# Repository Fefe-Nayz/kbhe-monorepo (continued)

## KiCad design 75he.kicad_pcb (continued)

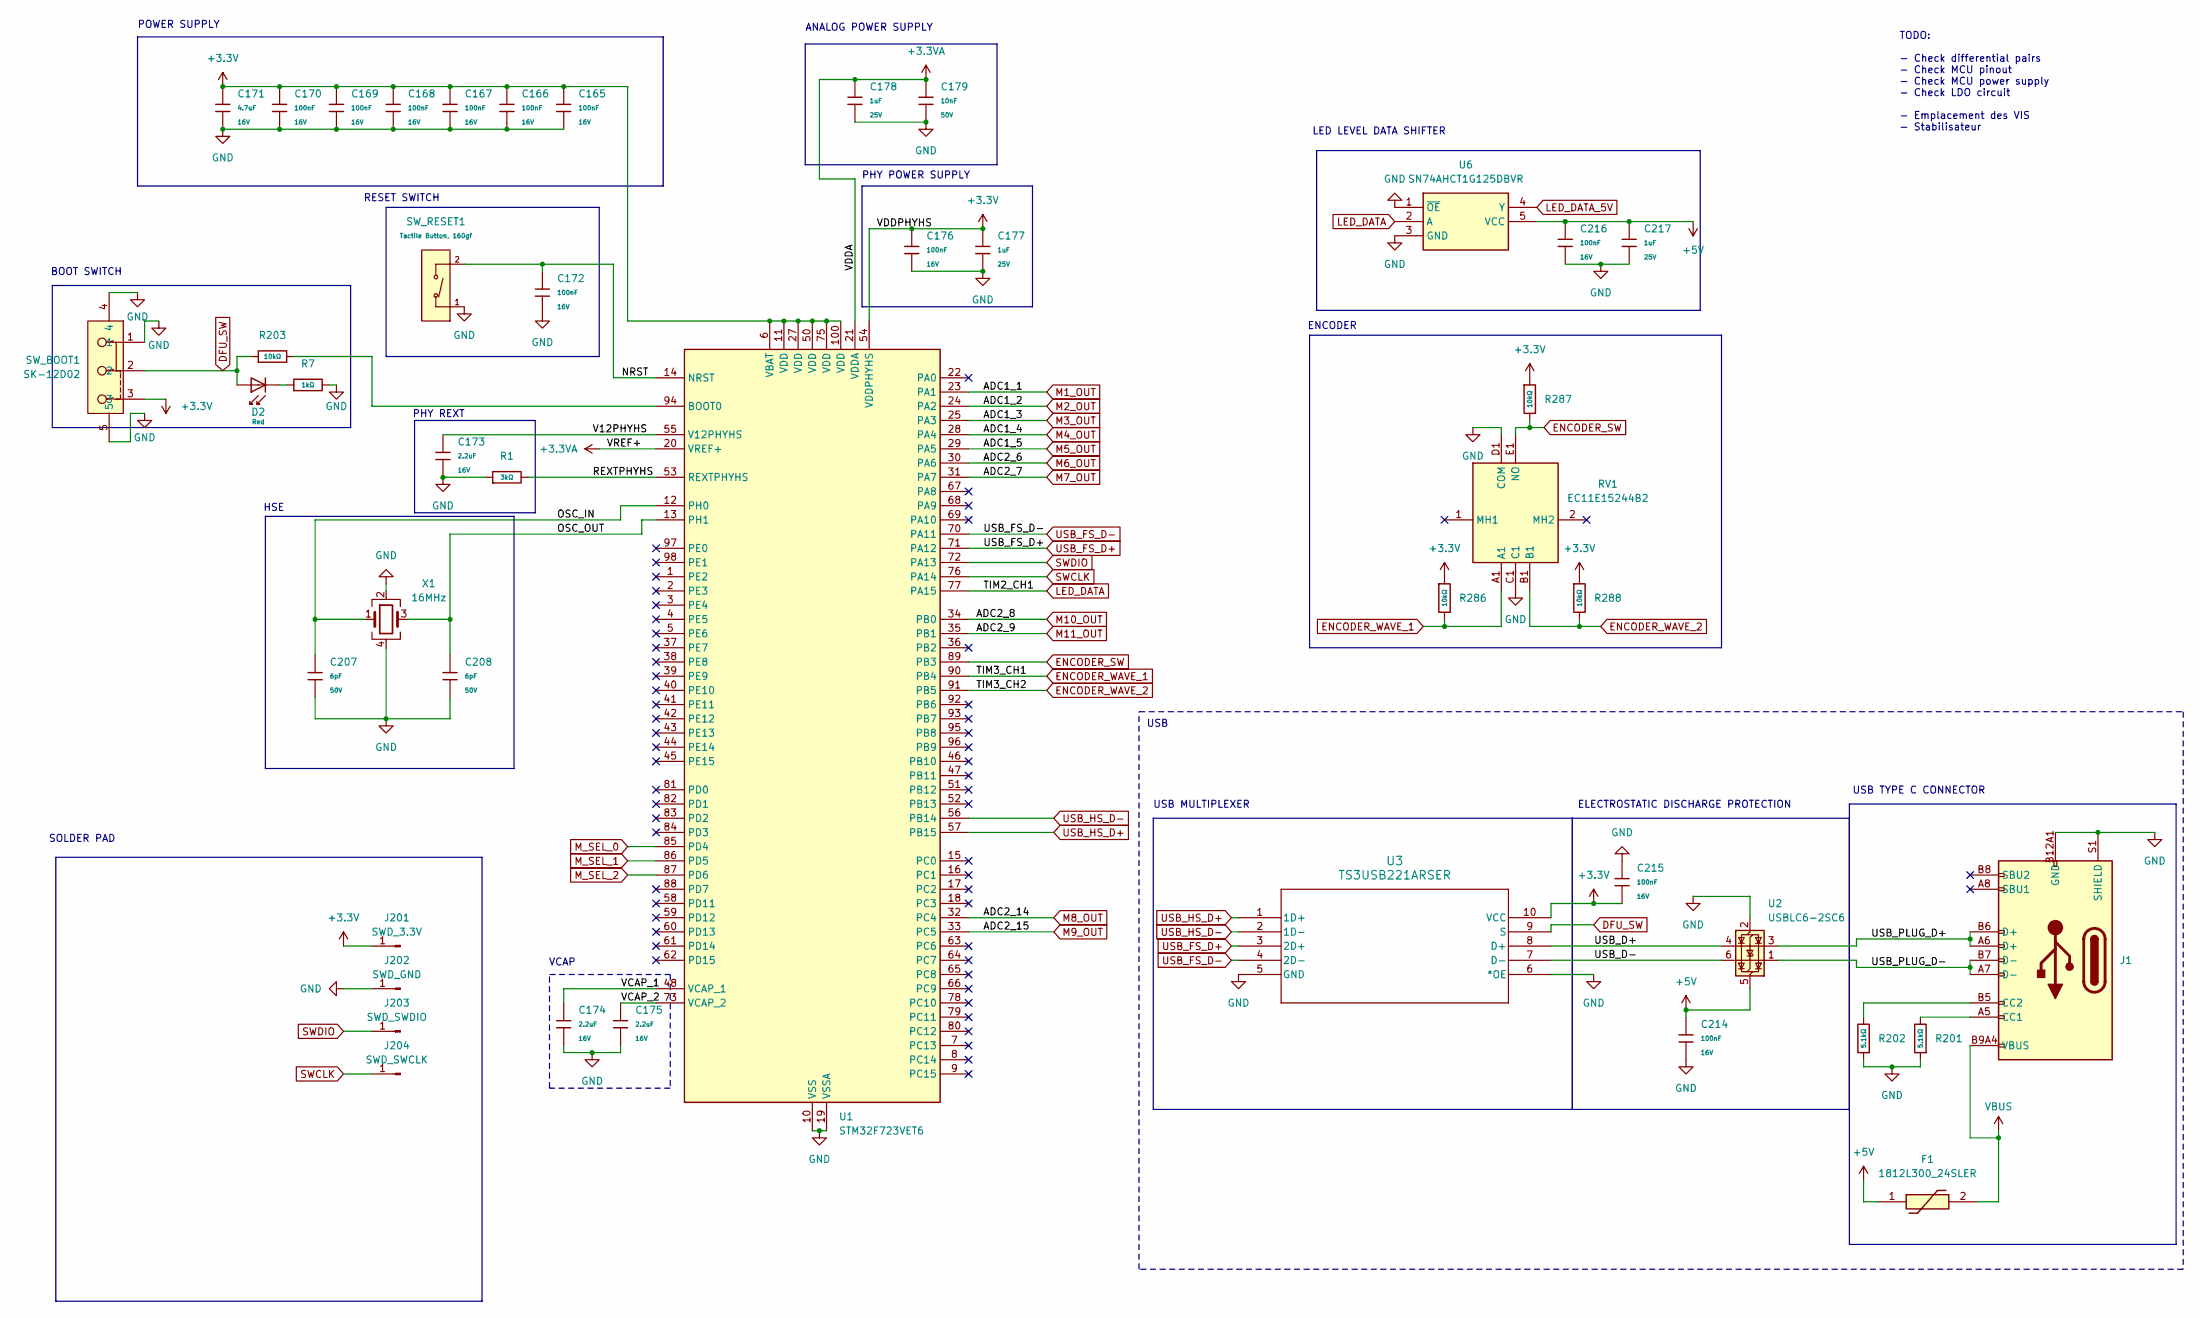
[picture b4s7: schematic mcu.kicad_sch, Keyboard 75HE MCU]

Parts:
C165, C166, C167, C168, C169, C170, C172, C176, C214, C215, C216: 100nF; C_0402; Voltage Rated 16V; Tolerance ±10%; Part CL05B104KO5NNNC; LCSC C1525
C171: 4.7uF; C_0603; Voltage Rated 16V; Tolerance ±10%; Part CL10A475KO8NNNC; LCSC C19666
C173, C174, C175: 2.2uF; C_0603; Voltage Rated 16V; Tolerance ±10%; Part CL10A225KO8NNNC; LCSC C23630
C177, C178, C217: 1uF; C_0402; Voltage Rated 25V; Tolerance ±10%; Part CL05A105KA5NQNC; LCSC C52923
C179: 10nF; C_0402; Voltage Rated 50V; Tolerance ±10%; Part CL05B103KB5NNNC; LCSC C15195
C207, C208: 6pF; C_0603; Voltage Rated 50V; Part 0603CG6R0C500NT; LCSC C37474
D2: Red; D_0603; Part KT-0603R; LCSC C2286
F1: 1812L300_24SLER; 1812L190SLPR; Mouser Part Number 576-1812L300/24SLER
J1: Connector, USB-TYPE-C-16P; TYPE-C-SMD_HX-TYPE-C-16PIN; LCSC C2927039
J201: SWD_3.3V; SolderWirePad_1x01_SMD_2x4mm
J202: SWD_GND; SolderWirePad_1x01_SMD_2x4mm
J203: SWD_SWDIO; SolderWirePad_1x01_SMD_2x4mm
J204: SWD_SWCLK; SolderWirePad_1x01_SMD_2x4mm
R1: 3kΩ; R_0603; Overload Voltage (Max) 75V; Tolerance ±1%; Part 0603WAF3001T5E; LCSC C4211
R7: 1kΩ; R_0402; Overload Voltage (Max) 50V; Tolerance ±1%; Part 0402WGF1001TCE; LCSC C11702
R201, R202: 5.1kΩ; R_0402; Overload Voltage (Max) 50V; Tolerance ±1%; Part 0402WGF5101TCE; LCSC C25905
R203, R286, R287, R288: 10kΩ; R_0402; Overload Voltage (Max) 50V; Tolerance ±1%; Part 0402WGF1002TCE; LCSC C25744
RV1: EC11E15244B2; Mouser Part Number 688-EC11E15244B2
SW_BOOT1: SK-12D02; SW-TH_SK-12D02VG3; LCSC Part C131374
SW_RESET1: Tactile Button, 160gf; SW_TS-1088-AR02016; Voltage Rating (Dc) 12V; Part TS-1088-AR02016; LCSC C720477
U1: STM32F723VET6; LQFP-100_14x14mm_P0.5mm
U2: USBLC6-2SC6; SOT-23-6
U3: TS3USB221ARSER; RSE10
U6: SN74AHCT1G125DBVR; SOT95P280X145-5N; Manufacturer_Part_Number SN74AHCT1G125DBVR; Mouser Part Number 595-SNAHCT1G125DBVR
X1: 16MHz; Crystal_SMD_2520-4Pin_2.5x2.0mm; LCSC C280836

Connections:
+3.3V: C165.1, C166.1, C167.1, C168.1, C169.1, C170.1, C171.1, C176.1, C177.1, C215.2, J201.1, R286.1, R287.1, R288.1, SW_BOOT1.3, U1.6 (VBAT), U1.11 (VDD), U1.27 (VDD), U1.50 (VDD), U1.54 (VDDPHYHS), U1.75 (VDD), U1.100 (VDD), U3.10 (VCC); also elsewhere on the board
+3.3VA: C178.1, C179.1, U1.20 (VREF+), U1.21 (VDDA); also elsewhere on the board
+5V: C214.1, C216.1, C217.1, F1.1, U2.5 (VBUS); also elsewhere on the board
/MCU/NRST: C172.1, SW_RESET1.2 (B), U1.14 (NRST)
/MCU/OSC_IN: C207.1, U1.12 (PH0), X1.1
/MCU/OSC_OUT: C208.1, U1.13 (PH1), X1.3
/MCU/REXTPHYHS: R1.2, U1.53 (REXTPHYHS)
/MCU/USB_D+: U2.4 (I/O2), U3.8 (D+)
/MCU/USB_D-: U2.6 (I/O1), U3.7 (D-)
/MCU/USB_PLUG_D+: J1.A6 (D+), J1.B6 (D+), U2.3 (I/O2)
/MCU/USB_PLUG_D-: J1.A7 (D-), J1.B7 (D-), U2.1 (I/O1)
/MCU/V12PHYHS: C173.1, U1.55 (V12PHYHS)
/MCU/VCAP_1: C174.1, U1.48 (VCAP_1)
/MCU/VCAP_2: C175.1, U1.73 (VCAP_2)
DFU_SW: D2.2, R203.1, SW_BOOT1.2, U3.9 (S)
ENCODER_SW: R287.2, RV1.E1 (NO), U1.89 (PB3)
ENCODER_WAVE_1: R286.2, RV1.A1, U1.90 (PB4)
ENCODER_WAVE_2: R288.2, RV1.B1, U1.91 (PB5)
GND: C165.2, C166.2, C167.2, C168.2, C169.2, C170.2, C171.2, C172.2, C173.2, C174.2, C175.2, C176.2, C177.2, C178.2, C179.2, C207.2, C208.2, C214.2, C215.1, C216.2, C217.2, J1.A12B1 (GND), J1.B12A1 (GND), J1.S1 (SHIELD), J202.1, R1.1, R7.2, R201.1, R202.1, RV1.C1, RV1.D1 (COM), SW_BOOT1.1, SW_BOOT1.4, SW_BOOT1.5, SW_RESET1.1 (A), U1.10 (VSS), U1.19 (VSSA), U1.26 (VSS), U1.49 (VSS), U1.74 (VSS), U1.99 (VSS), U2.2 (GND), U3.5 (GND), U3.6 (*OE), X1.2, X1.4; also elsewhere on the board
LED_DATA: U1.77 (PA15), U6.2 (A)
M1_OUT: U1.23 (PA1); also elsewhere on the board
M2_OUT: U1.24 (PA2); also elsewhere on the board
M3_OUT: U1.25 (PA3); also elsewhere on the board
M4_OUT: U1.28 (PA4); also elsewhere on the board
M5_OUT: U1.29 (PA5); also elsewhere on the board
M6_OUT: U1.30 (PA6); also elsewhere on the board
M7_OUT: U1.31 (PA7); also elsewhere on the board
M8_OUT: U1.32 (PC4); also elsewhere on the board
M9_OUT: U1.33 (PC5); also elsewhere on the board
M10_OUT: U1.34 (PB0); also elsewhere on the board
M11_OUT: U1.35 (PB1); also elsewhere on the board
M_SEL_0: U1.85 (PD4); also elsewhere on the board
M_SEL_1: U1.86 (PD5); also elsewhere on the board
M_SEL_2: U1.87 (PD6); also elsewhere on the board
unnamed: D2.1, R7.1
unnamed: J1.A5 (CC1), R201.2
unnamed: J1.B5 (CC2), R202.2
unnamed: R203.2, U1.94 (BOOT0)
SWCLK: J204.1, U1.76 (PA14)
SWDIO: J203.1, U1.72 (PA13)
USB_FS_D+: U1.71 (PA12), U3.3 (2D+)
USB_FS_D-: U1.70 (PA11), U3.4 (2D-)
USB_HS_D+: U1.57 (PB15), U3.1 (1D+)
USB_HS_D-: U1.56 (PB14), U3.2 (1D-)
VBUS: F1.2, J1.A9B4 (VBUS), J1.B9A4 (VBUS)

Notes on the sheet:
HSE
ANALOG POWER SUPPLY
PHY POWER SUPPLY
TODO: - Check differential pairs - Check MCU pinout - Check MCU power supply - Check LDO circuit - Emplacement des VIS - Stabilisateur
USB TYPE C CONNECTOR
ELECTROSTATIC DISCHARGE PROTECTION
SOLDER PAD
LED LEVEL DATA SHIFTER
VCAP
BOOT SWITCH
ENCODER
RESET SWITCH
USB MULTIPLEXER
USB
POWER SUPPLY
PHY REXT

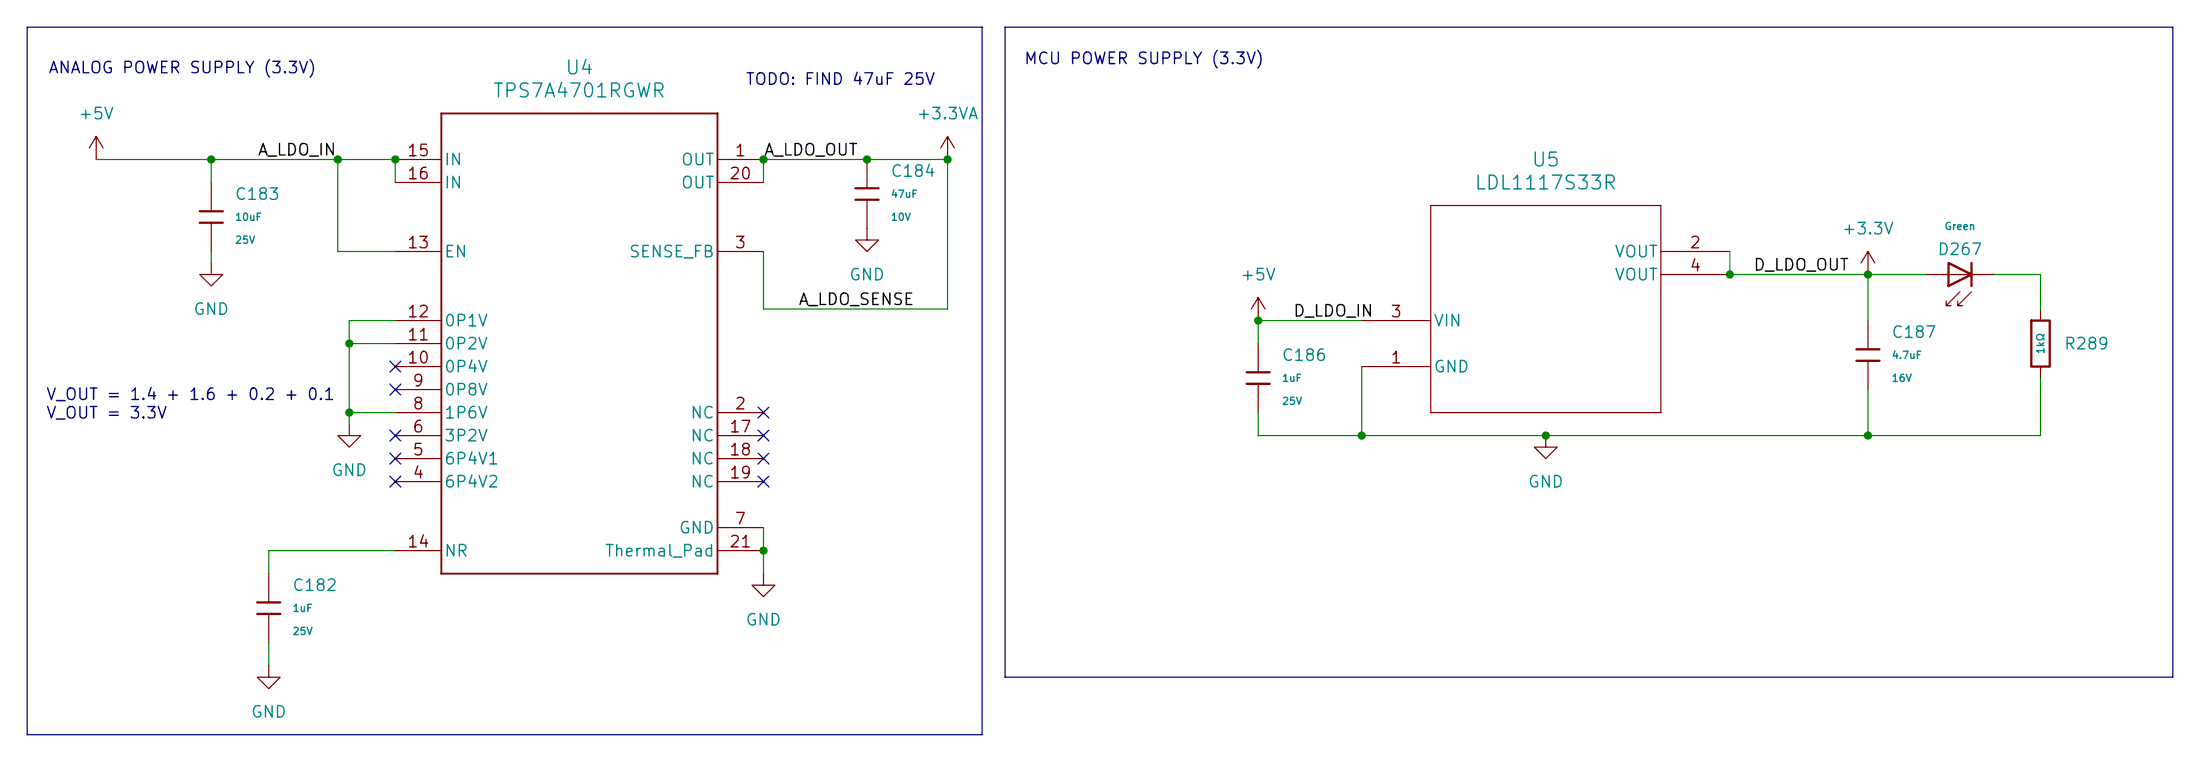
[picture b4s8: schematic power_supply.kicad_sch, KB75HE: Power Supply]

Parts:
C182, C186: 1uF; C_0402; Voltage Rated 25V; Tolerance ±10%; Part CL05A105KA5NQNC; LCSC C52923
C183: 10uF; C_0805; Voltage Rated 25V; Tolerance ±10%; Part CL21A106KAYNNNE; LCSC C15850
C184: 47uF; C_1206; Voltage Rated 10V; Tolerance ±20%; Part CL31A476MPHNNNE; LCSC C96123
C187: 4.7uF; C_0603; Voltage Rated 16V; Tolerance ±10%; Part CL10A475KO8NNNC; LCSC C19666
D267: Green; D_0805; Part KT-0805G; LCSC C2297
R289: 1kΩ; R_0402; Overload Voltage (Max) 50V; Tolerance ±1%; Part 0402WGF1001TCE; LCSC C11702
U4: TPS7A4701RGWR; RGW0020A-IPC_A; LCSC C90084
U5: LDL1117S33R; SOT223_STM

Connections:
+3.3V: C187.1, D267.2, U5.2 (VOUT), U5.4 (VOUT); also elsewhere on the board
+3.3VA: C184.1, U4.1 (OUT), U4.3 (SENSE_FB), U4.20 (OUT); also elsewhere on the board
+5V: C183.1, C186.1, U4.13 (EN), U4.15 (IN), U4.16 (IN), U5.3 (VIN); also elsewhere on the board
GND: C182.2, C183.2, C184.2, C186.2, C187.2, R289.2, U4.7 (GND), U4.8 (1P6V), U4.11 (0P2V), U4.12 (0P1V), U4.21 (Thermal_Pad), U5.1 (GND); also elsewhere on the board
unnamed: D267.1, R289.1
unnamed: C182.1, U4.14 (NR)

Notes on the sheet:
TODO: FIND 47uF 25V
ANALOG POWER SUPPLY (3.3V)
V_OUT = 1.4 + 1.6 + 0.2 + 0.1 V_OUT = 3.3V
MCU POWER SUPPLY (3.3V)

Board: 6 copper layers, 629 parts (383 on the bottom side), 276 nets, no tracks yet.

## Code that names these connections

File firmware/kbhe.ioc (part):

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Mcu.Name=STM32F723V(C-E)Tx
Mcu.Package=LQFP100
Mcu.UserName=STM32F723VETx
PA1.Signal=ADCx_IN1
PA13.Mode=Serial_Wire
PA13.Signal=SYS_JTMS-SWDIO
PA14.Mode=Serial_Wire
PA14.Signal=SYS_JTCK-SWCLK
PA15.GPIOParameters=GPIO_Label,GPIO_Speed
PA15.GPIO_Label=LED_DATA
PA15.GPIO_Speed=GPIO_SPEED_FREQ_VERY_HIGH
PA15.Signal=S_TIM2_CH1
PA2.Signal=ADCx_IN2
PA3.Signal=ADCx_IN3
PA4.Signal=ADCx_IN4
PA5.Signal=ADCx_IN5
PA6.Signal=ADCx_IN6
PA7.Signal=ADCx_IN7
PB0.Signal=ADCx_IN8
PB1.Signal=ADCx_IN9
PB3.GPIOParameters=GPIO_PuPd,GPIO_Label,GPIO_Speed
PB3.GPIO_Label=ENCODER_SW
PB3.GPIO_PuPd=GPIO_PULLUP
PB3.GPIO_Speed=GPIO_SPEED_FREQ_LOW
PB3.Signal=GPIO_Input
PB4.GPIOParameters=GPIO_PuPd,GPIO_Label,GPIO_Speed
PB4.GPIO_Label=ENCODER_WAVE_2
PB4.GPIO_PuPd=GPIO_PULLUP
PB4.GPIO_Speed=GPIO_SPEED_FREQ_LOW
PB4.Signal=GPIO_Input
PB5.GPIOParameters=GPIO_PuPd,GPIO_Label,GPIO_Speed
PB5.GPIO_Label=ENCODER_WAVE_1
PB5.GPIO_PuPd=GPIO_PULLUP
PB5.GPIO_Speed=GPIO_SPEED_FREQ_LOW
PB5.Signal=GPIO_Input
PB14.Mode=Internal_Phy_Device
PB14.Signal=USB_OTG_HS_DM
PB15.Mode=Internal_Phy_Device
PB15.Signal=USB_OTG_HS_DP
PC4.Signal=ADCx_IN14
PC5.Signal=ADCx_IN15
PD4.GPIOParameters=GPIO_Speed,GPIO_Label
PD4.GPIO_Label=M0
PD4.GPIO_Speed=GPIO_SPEED_FREQ_VERY_HIGH
PD4.Signal=GPIO_Output
PD5.GPIOParameters=GPIO_Speed,GPIO_Label
PD5.GPIO_Label=M1
PD5.GPIO_Speed=GPIO_SPEED_FREQ_VERY_HIGH
PD5.Signal=GPIO_Output
PD6.GPIOParameters=GPIO_Speed,GPIO_Label
PD6.GPIO_Label=M2
PD6.GPIO_Speed=GPIO_SPEED_FREQ_VERY_HIGH
PD6.Signal=GPIO_Output
PH0-OSC_IN.Mode=HSE-External-Oscillator
PH0-OSC_IN.Signal=RCC_OSC_IN
PH1-OSC_OUT.Mode=HSE-External-Oscillator
PH1-OSC_OUT.Signal=RCC_OSC_OUT
RCC.HSE_VALUE=16000000
RCC.SYSCLKFreq_VALUE=216000000
RCC.SYSCLKSource=RCC_SYSCLKSOURCE_PLLCLK
board=custom

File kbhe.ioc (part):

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Mcu.Name=STM32F723V(C-E)Tx
Mcu.Package=LQFP100
Mcu.UserName=STM32F723VETx
PA0-WKUP.Signal=ADCx_IN0
PA1.Signal=ADCx_IN1
PA13.Mode=Serial_Wire
PA13.Signal=SYS_JTMS-SWDIO
PA14.Mode=Serial_Wire
PA14.Signal=SYS_JTCK-SWCLK
PA2.Signal=ADCx_IN2
PA3.Signal=ADCx_IN3
PB14.Mode=Internal_Phy_Device
PB14.Signal=USB_OTG_HS_DM
PB15.Mode=Internal_Phy_Device
PB15.Signal=USB_OTG_HS_DP
PC0.Signal=ADCx_IN10
PC1.Signal=ADCx_IN11
PC11.GPIOParameters=GPIO_Speed,GPIO_Label
PC11.GPIO_Label=M3
PC11.GPIO_Speed=GPIO_SPEED_FREQ_VERY_HIGH
PC11.Signal=GPIO_Output
PC12.GPIOParameters=GPIO_Speed,GPIO_Label
PC12.GPIO_Label=M2
PC12.GPIO_Speed=GPIO_SPEED_FREQ_VERY_HIGH
PC12.Signal=GPIO_Output
PC2.Signal=ADCx_IN12
PC3.Signal=ADCx_IN13
PC7.GPIOParameters=GPIO_Label,GPIO_Speed
PC7.GPIO_Label=LED_DATA
PC7.GPIO_Speed=GPIO_SPEED_FREQ_VERY_HIGH
PC7.Signal=S_TIM3_CH2
PD0.GPIOParameters=GPIO_Speed,GPIO_Label
PD0.GPIO_Label=M1
PD0.GPIO_Speed=GPIO_SPEED_FREQ_VERY_HIGH
PD0.Signal=GPIO_Output
PD1.GPIOParameters=GPIO_Speed,GPIO_Label
PD1.GPIO_Label=M0
PD1.GPIO_Speed=GPIO_SPEED_FREQ_VERY_HIGH
PD1.Signal=GPIO_Output
PH0-OSC_IN.Mode=HSE-External-Oscillator
PH0-OSC_IN.Signal=RCC_OSC_IN
PH1-OSC_OUT.Mode=HSE-External-Oscillator
PH1-OSC_OUT.Signal=RCC_OSC_OUT
RCC.HSE_VALUE=16000000
RCC.SYSCLKFreq_VALUE=216000000
RCC.SYSCLKSource=RCC_SYSCLKSOURCE_PLLCLK
board=custom

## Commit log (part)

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2025-12-25 feat: dma scan
2025-12-25 optimisation
2025-12-27 tinyusb init
2025-12-28 feat: hid
2025-12-29 store raw values
2025-12-29 fix: improve performance by enabling instruction caches
2025-12-29 chore: add docs
2025-12-29 fix: fix & review trigger
2025-12-30 feat: add data cache & mpu for dma
2026-01-01 fix: make filtering in main loop
2026-01-12 fix: led effect settings now saved, no more settings save failed message
2026-01-25 SideBar error fixed - /hooks/use-mobile.ts was missing and Sidebar added to project
2026-01-25 Two new pages added and IconSun added for theme
2026-01-29 Key mapping logic setup - start
2026-01-31 Trying to fix a few things and make the UI responsive
2026-01-31 Started implementing keyboard keys selection and installed zustand to reuse baseKeyboard on any page with the current layout
2026-02-01 Just displayed the devices informations and handle multiple device showed v2
2026-02-02 final switch layout
2026-02-04 add capacitor to mux vcc
2026-02-04 start usb
2026-02-05 place sensors
2026-02-06 compute diff pair spacing
2026-02-07 finish sensor out capacitor
2026-02-07 continue sensor out
2026-02-13 Trying to implement store copy pasting and tweeking templates from ChatGPT and online articles
2026-03-18 added power led, some cleanup/fixes, added doc
2026-03-19 adjust schematic text
2026-03-19 Add WS2812 footprints, resistors and net names
    Replace generic switch footprints with proper SMD components and metadata: add WS2812B RGB LED footprints (with pads, nets, 3D models and part/Datasheet/LCSC info), add many resistor footprints and d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
2026-03-19 clean PCB
2026-03-19 mux placement & mcu placement
2026-03-20 mcu capacitor, usb port, ldo
2026-03-20 mounting hole
2026-03-21 Placed led
2026-03-21 Update switch footprints: version & 3D models
    Bump footprint metadata and standardize footprints for various switch sizes. Updated (version) and (generator_version) to 20260206 / 10.0, refreshed UUIDs, and set duplicate_pad_numbers_are_jumpers t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
2026-03-21 fix: led align
2026-03-21 fix: sensors bad out label
2026-03-22 revert: revert to finish led capacitor after crash
2026-03-22 led capacitor & sensor capacitor & fixes
2026-03-22 lcsc part
2026-03-22 add jlc drc & route mux select
2026-03-22 continue route
2026-03-23 plan
2026-03-24 wired new muxes
2026-03-25 finish power led
2026-03-28 add cahier des charges
2026-03-28 Add PySide6 Qt GUI and protocol/device fixes
    Introduce a new PySide6-based GUI (kbhe_tool/qtgui) with app, pages, common widgets, theme and session management, plus keyboard-layout.json. Update cli to launch the new Qt GUI and re-export KBHECon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
2026-03-29 Split LED matrix static/runtime + live UI
    Refactor LED matrix internals to separate a persisted, software-editable matrix (pixels_static) from the runtime frame (pixels_runtime) used for effects and third-party/live control. Add LED_EFFECT_T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
2026-03-29 keyboard-store created
2026-03-30 refactor: move LUT to int
2026-04-04 refactor: create module for analog & mux
2026-04-04 refactor: calibration
2026-04-05 fix: keyboard store implementation
2026-04-05 App.tsx modified
2026-04-05 App.tsx updated
2026-04-07 refactor: rename hid file
2026-04-08 fix: set min calibration
2026-04-08 Clean up LED bring-up and defaults
2026-04-08 Adjust DEFAULT_BASE_LAYER keymap
2026-04-08 feat: new lut
2026-04-09 Add rotary encoder settings, UI, and effects
    Introduce full rotary encoder configuration and tooling: add settings structures and APIs, protocol commands (GET/SET_ROTARY_ENCODER_SETTINGS), and HID consumer mute. Implement runtime handling in fi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
2026-04-09 Add LED output override and 82-key SignalRGB
    Introduce a high-priority LED output override and runtime state reset hooks, and expand the SignalRGB plugin to the full 82-key layout.
    Changes include:
    - led_matrix: add an output-override pixel buffer and API (set/clear) and prefer the override frame when active; initialize/clear override on init and update display immediately when changed.
    - analog/calibration: use the new output-override for guided calibration frames, restore runtime LED state via clearing the override, and expose calibration_guided_is_active().
    - hid/layout: add keyboard_hid_reset_state() and layout_reset_state() to clear internal bookkeeping without sending reports.
    - trigg
2026-04-09 Color picker component added
2026-04-10 Add mouse, diagnostics, and advanced gamepad features
    Introduce mouse HID and diagnostics subsystems and extend gamepad/trigger/settings functionality. Added new headers and implementations for mouse_hid and diagnostics, integrated diagnostics-driven pr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
2026-04-10 Modification of keys settings
2026-04-10 Expose MCU metrics and LED effect color
    Add runtime MCU telemetry and LED-effect color support across firmware and tooling.
    Firmware:
    - HID protocol: add CMD_GET_LED_EFFECT_COLOR and CMD_GET_MCU_METRICS and a packed hid_resp_mcu_metrics_t response struct; implement handlers to return persisted LED effect color and live MCU metrics.
    - Runtime metrics: sample internal VREF/temperature via injected ADC, compute smoothed scan/work timings and load (permille), store live values (mcu_*_live), and sample at ~1s when diagnostics perf i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
    - LED: switch pixel source for get_pixel to led_matrix_get_raw_data(), add led_matrix_nudge_host_volume_overlay() and constant HOST_VOLUME_STEP_ESTIMATE to
2026-04-11 Append-only flash storage and autosave settings
    Introduce an append-only flash storage format with record headers, CRC32, sequence numbers and legacy raw layout detection; implement scanning, aligned writes, and consolidation via sector erase. Rep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
    Add a deferred autosave system in settings: mark-dirty on live changes, a change counter, settings_task(now_ms) to service delayed saves after a short idle (SETTINGS_AUTOSAVE_DELAY_MS), and settings_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
    Update many settings sette
2026-04-11 Add AppShell, new pages, query client & deps
    Introduce a new app shell and many UI components/pages as part of a large refactor. Added AppShell, shared UI components (KeyboardPreviewCard, LayerSelector, LiveStatusChip, PageLayout, SectionCard),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
2026-04-11 Add UI color picker and live update handlers
    Introduce a new color picker UI (src/components/ui/color-picker.tsx) and migrate the existing ColorPicker to use it. Add live-preview support via onLiveChange to AnalogCurveEditor, DistanceSlider and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
2026-04-12 Add firmware drag-and-drop & tweak curves
    Add drag-and-drop firmware import (desktop/browser) and improve firmware file UX. Firmware.tsx: integrate Tauri window drag events, implement drag/drop handlers and drop zone ref, parse text/URI drop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
2026-04-13 Clear keyboard HID state when disabled
    Prioritize the keyboard master switch and ensure keyboard HID state is cleared when keyboard output is turned off.
    - layout.c: Add an early check so the keyboard master switch always inhibits keyboard emission (returns false if keyboard is disabled) before considering gamepad routing.
    - settings.c: Include keyboard HID headers and, when disabling the keyboard (either via settings_set_keyboard_enabled or by changing options), release all keys and reset keyboard/NKRO state to avoid 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
    This prevents stuck or stale keyboard reports after toggling keyboard output and makes routing logic deterministic by giving the master switch priority.
2026-04-13 Add atomic sendCommand with fallback
    Introduce an atomic sendCommand path via a new Tauri command (kbhe_send_command) and a transport.sendCommand wrapper that uses invoke. KbheCommander now tries the atomic path first, caches availabili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
2026-04-13 Refactor Lighting UI: KeyboardEditor + matrix preview
    Replace the old tabbed Effects/Matrix UI with a unified KeyboardEditor layout and live keyboard preview. Key changes:
    - Introduce KeyboardEditor wrapper and menubar, consolidate left/right columns into a single responsive layout.
    - Add keyboard preview that shows either a MatrixKeyboard (editable in matrix mode) or a read-only BaseKeyboard with per-key colors.
    - Remove tab state (activeTab) and related Tabs/ScrollArea code.
    - Add local cache helper (updateMatrixPixelsLocal) and update LED-related mutations (fill, clear, rainbow, upload) to update local matrix pixels and set React Query data instead of relying solely on 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
    - Adjus
2026-04-13 refactor: calibration page, select outline, detect keybooard in updater mode
2026-04-13 fix: settings
2026-04-16 Add audio spectrum, flasher, and Windows Mica
    Introduce platform audio spectrum capture and firmware flashing, plus Windows Mica UI styling.
    - Backend: add a new src-tauri/src/audio.rs implementing WASAPI loopback capture, FFT (rustfft) based band extraction, AGC and per-band smoothing; expose tauri command kbhe_get_audio_bands. Add rustf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
    - Backend: implement firmware updater flow in commands.rs (updater protocol, CRC32, transactions, data chunking, BEGIN/DATA/FINISH/BOOT/ABORT) and expose kbhe_flash_firmware; emits kbhe_flash_progres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
    - Fronte
2026-04-16 Async flash saves & third-party LED live mode
    Introduce non-blocking flash writes and deferred settings persistence, plus runtime-only LED streaming and WS2812 batching.
    - Add flash_storage asynchronous API: flash_storage_write_async_begin/step/is_busy and flash_storage_async_result_t to program flash in incremental steps.
    - Implement settings_request_save() and snapshot-based async save: settings_task() now schedules and drives async flash writes (configurable words/step), preserves a snapshot to avoid races, and hand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
    - Keep settings non-blocking in HID handlers by switching CMD
2026-04-16 Alpha mask, audio, protocol & UI improvements
    Introduce alpha-key masking and audio/LED enhancements and various UI fixes.
    Details:
    - Add useAlphaMaskService: computes per-key alpha bitmask from OS layout and base layer keycodes and sends SET_LED_ALPHA_MASK to device when ALPHA_MODS is active.
    - Protocol & device API: add SET_LED_ALPHA_MASK command, BASS_RIPPLE effect, ENUM param type; extend KBHEDevice with DeviceOptions, getOptions, setOptions, setLedThermalProtectionEnabled and setAlpha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
    - Profile sync: applyFirmwareProfileSnapshot now uses setOptions and supports led_thermal_protection_enabled.
    - Audio spectrum service: smoother, timed loop with envelope tracking; supports IMPACT_RA
2026-04-16 Add LED alpha mask and thermal protection option
    Expose LED thermal protection in the HID options and add support for a host-controlled LED alpha mask. Changes include: new CMD_SET_LED_ALPHA_MASK (0x7A) in the protocol header, added led_thermal_pro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
2026-04-19 Clear WS2812 LEDs when output disabled
    WS2812 LEDs retain the last frame until a new one is transmitted. When output is fully disabled (for example when a Caps Lock overlay turns off), explicitly zero the LED buffer and call ws2812_show t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
2026-04-24 Add gamepad legend overlay to keyboard preview
    Introduce a keyLegendOverlayMap to render gamepad/keyboard combined overlays on key previews. Prop is threaded through BaseKeyboard → KeyboardLayout → KeyboardKey, with CSS for overlay styling. useKe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
2026-04-25 Create tinyusb
2026-04-26 Reorganize KiCad libraries; add Legacy Docs
    Large repository reorganization of KiCad assets: added Docs and Legacy/ proto directories with many component datasheets and legacy project files, moved and renamed numerous footprints, 3D models and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
2026-04-26 Code formatting: whitespace and indentation fixes
    Minor formatting changes in KBHEDevice and Lighting components to match project style/linter. device.ts: adjust constructor brace spacing. Lighting.tsx: fix indentation for enum fallback expression a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
2026-04-26 Import and organize KBHE projects
2026-04-26 Track binary assets with Git LFS
2026-04-26 Display app version and restrict dev firmware UI
    Bump configurator version to 0.1.1 (package.json, Cargo.toml, tauri.conf.json). Add Tauri app version query in AppSettings and show an "About" card with the app version. Gate firmware file picker and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
2026-04-26 Bump firmware to v2.0.0 and update README TODOs
    Increase FIRMWARE_VERSION from 0x0109 (v1.9.0) to 0x0200 (v2.0.0) in firmware/Core/Src/settings.c. Add a "Current limitations - TODOs" section to README.md listing known hardware/firmware tasks (tran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
2026-04-26 Reorganize assets and update README images
    Move and rename many image assets into a clearer folder structure (assets/photos/* and assets/cad/75he-exploded/) and add several new photos (PCB top/bottom, MCU test boards, TIPE multiplexer, config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
2026-04-26 Relocate PCB render images and update README
    Move PCB render PNGs out of assets/exports/renders into their parent assets/ directories for proto-6-key-hall-sensors, proto-mcu-v1, and proto-mcu-v2 (file content unchanged). Update README image lin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
2026-04-26 Add dashboard MCU trends service and UI tweaks
    Introduce a background service and persistent store for MCU metric trends, refactor Dashboard to consume the store, and apply several UI/splashscreen refinements.
    Changes include:
    - Add zustand store apps/configurator/src/stores/dashboard-mcu-trends-store.ts to hold rolling MCU metric trends.
    - Add useDashboardMcuTrendsService hook apps/configurator/src/lib/kbhe/useDashboardMcuTrendsService.ts to poll MCU metrics in background and push to the store.
    - Refactor Dashboard (apps/configurator/src/pages/Dashboard.tsx) to read trends from the new store and remove local trend state and inline polling.
    - Persist keyboard editor panel layout using react
2026-04-26 fix autostart
2026-05-23 Add 75he legacy PCB KiCad projects
    Introduce hardware/pcb/75he/Legacy containing source-only KiCad project archives for proto-6-key-hall-sensors, proto-mcu-v1, and proto-mcu-v2. Each project includes reduced local libraries (Library/F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
2026-06-11 chore: lut improvement & script update
2026-06-11 fix: missing LUT zero reference value
